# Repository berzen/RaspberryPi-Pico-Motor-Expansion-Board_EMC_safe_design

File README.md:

power supply: 
- 35mmx20mm instead of 55mmx22mm (43% reduction)
 - update of components:
    - ch224a vs ch224k (ch224k should be replaced regarding IC supplier)
    - 12pin USB vs 6pin USB (connection of USB lines - additional PD profiles possible)
    - impedance controlled connection for DP, DN, CC1, CC2 lines (for JLCPCB 2 layer stackup)
    - 20V VBUS vs 12V VBUS (less current)
    - LMR51635 vs TPS5450 (smaller size, less additional components)
    - cost reduction of BOM costs
    - 2 layer PCB vs 4 layer PCB
    - EMC safe design

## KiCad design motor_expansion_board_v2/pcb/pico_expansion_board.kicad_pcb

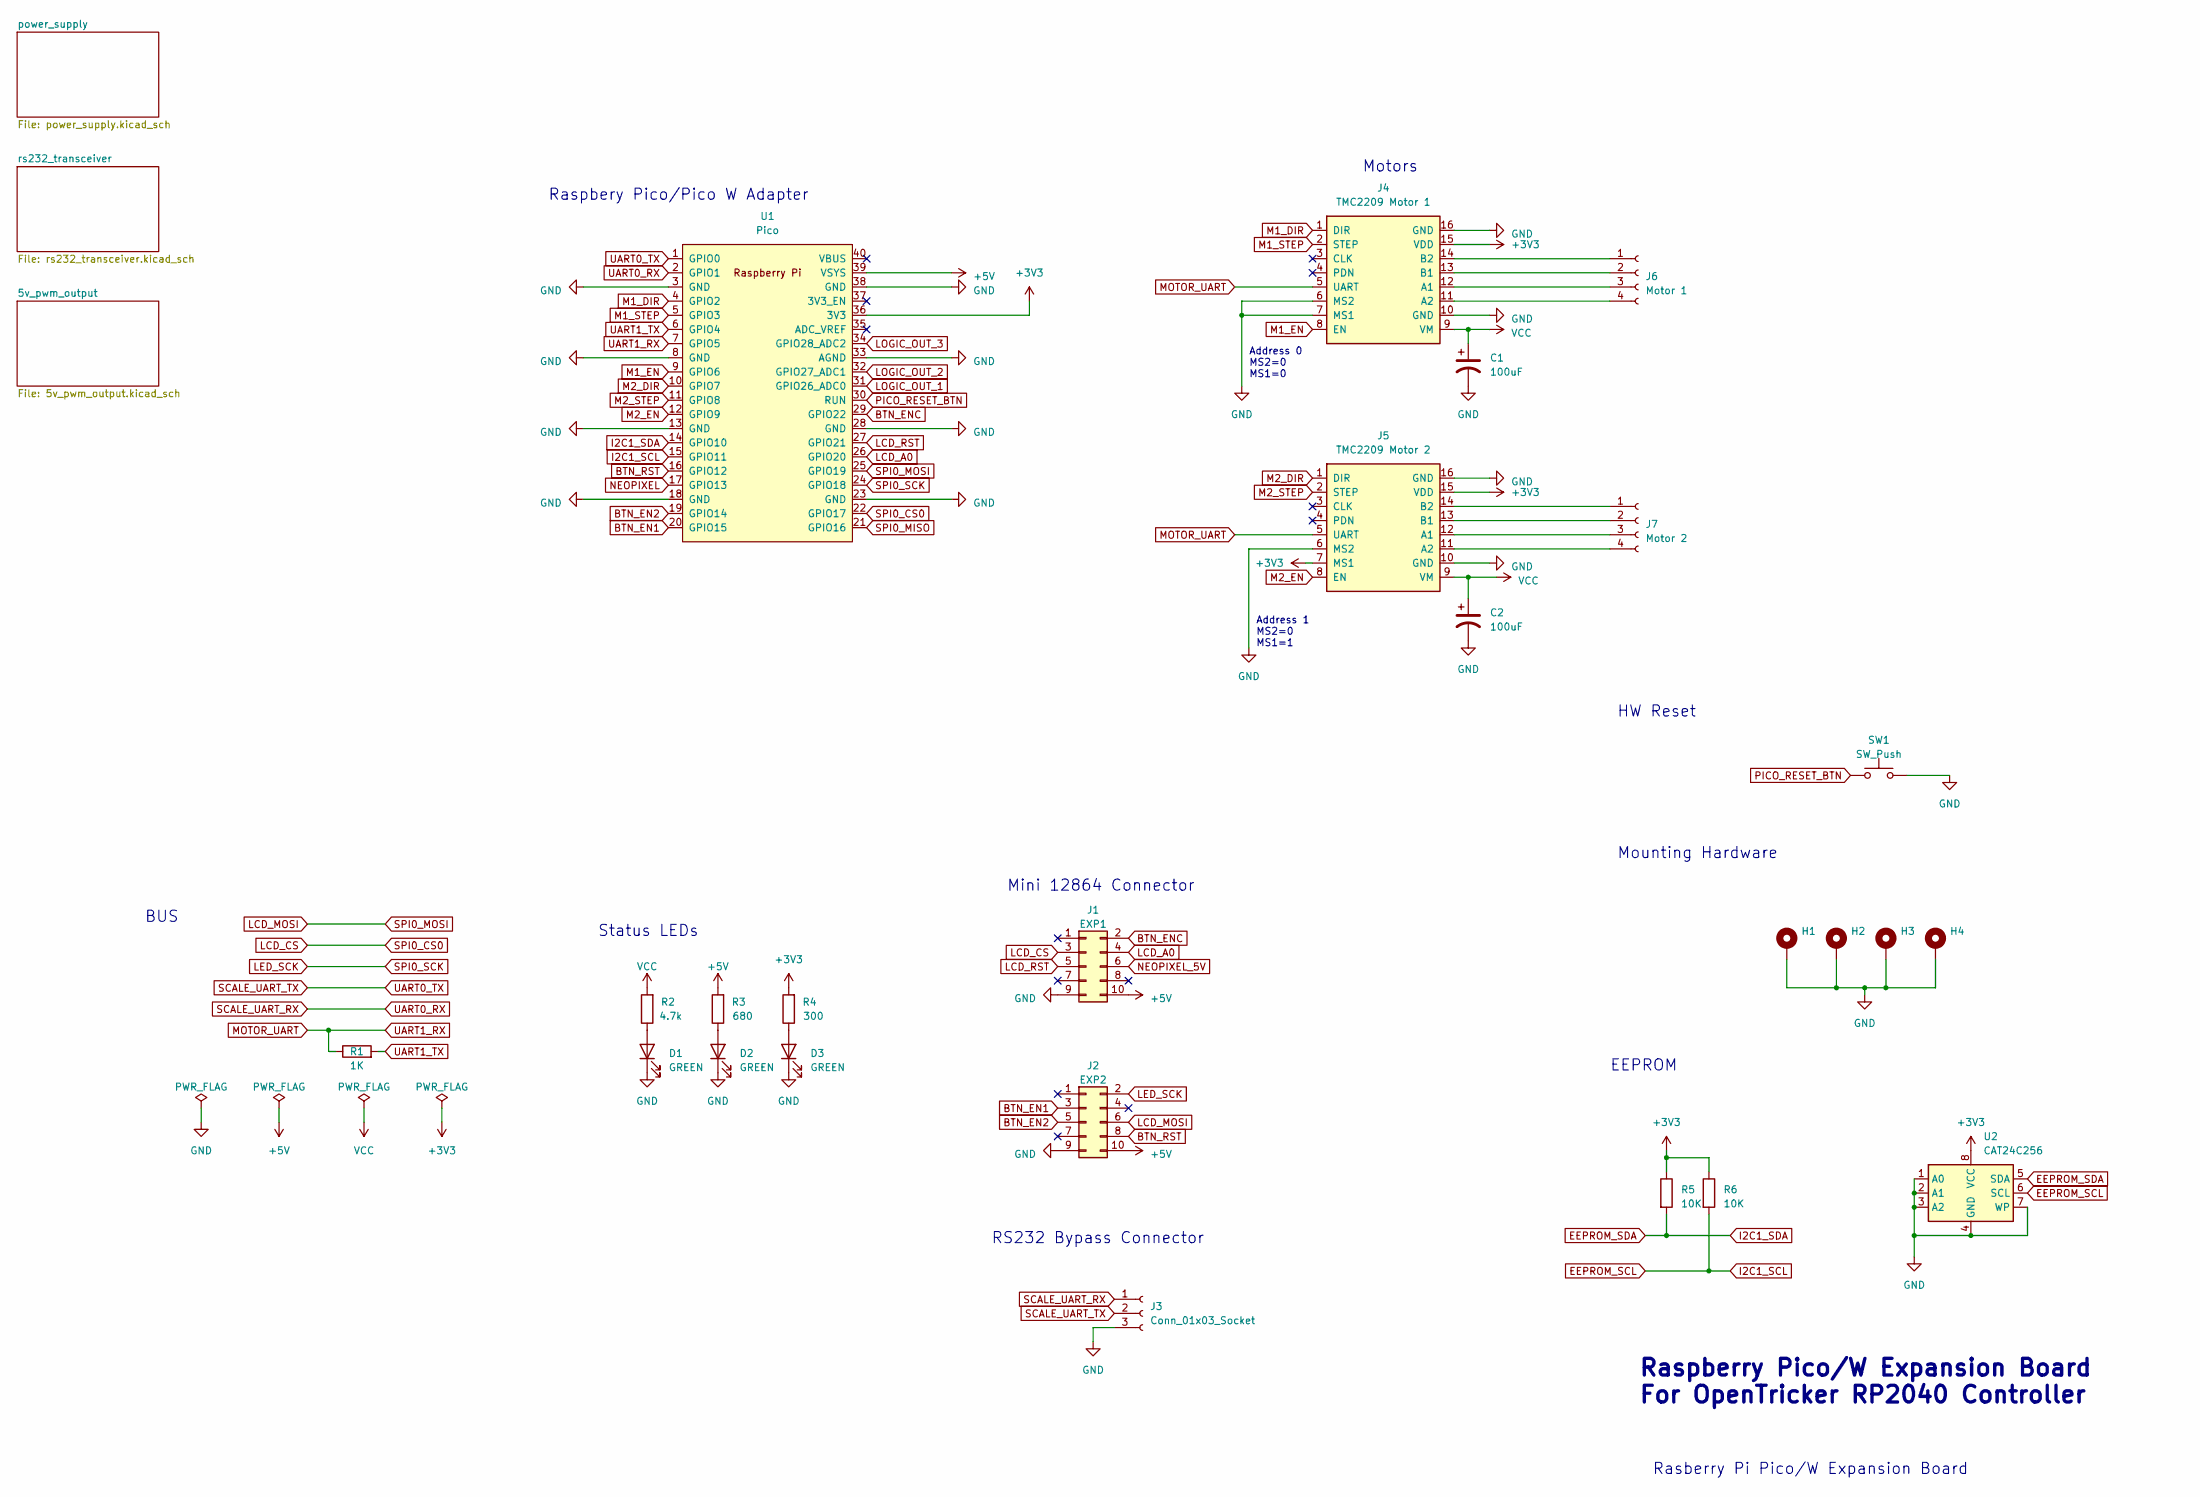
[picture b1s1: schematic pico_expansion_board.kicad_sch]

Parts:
C1, C2: 100uF; CP_Elec_6.3x7.7; LCSC Part # C2836442
D1, D2, D3: GREEN; D_0805_2012Metric_Pad1.15x1.40mm_HandSolder; LCSC Part # C84257
H1, H2, H3, H4: MountingHole_3.2mm_M3_Pad_Via
J1: EXP1; IDC-Header_2x05_P2.54mm_Vertical; LCSC Part # C2977596
J2: EXP2; IDC-Header_2x05_P2.54mm_Vertical; LCSC Part # C2977596
J3: Conn_01x03_Socket; JST_XH_B3B-XH-A_1x03_P2.50mm_Vertical; LCSC Part # C158003
J4: TMC2209 Motor 1; Conn_StepStick_smaller_hole; LCSC Part # C27438
J5: TMC2209 Motor 2; Conn_StepStick_smaller_hole; LCSC Part # C27438
J6: Motor 1; JST_XH_B4B-XH-A_1x04_P2.50mm_Vertical; LCSC Part # C144395
J7: Motor 2; JST_XH_B4B-XH-A_1x04_P2.50mm_Vertical; LCSC Part # C144395
R1: 1K; R_0805_2012Metric_Pad1.20x1.40mm_HandSolder; LCSC Part # C17513
R2: 4.7k; R_0805_2012Metric_Pad1.20x1.40mm_HandSolder; LCSC Part # C17673
R3: 680; R_0805_2012Metric_Pad1.20x1.40mm_HandSolder; LCSC Part # C17798
R4: 300; R_0805_2012Metric_Pad1.20x1.40mm_HandSolder; LCSC Part # C17617
R5, R6: 10K; R_0805_2012Metric_Pad1.20x1.40mm_HandSolder; LCSC Part # C17414
SW1: SW_Push; SW_Push_1P1T_NO_6x6mm_H9.5mm; LCSC Part # C2837532
U1: Pico; RPi_Pico_FootprintOnly; LCSC Part # C429947
U2: CAT24C256; SO-8_3.9x4.9mm_P1.27mm; LCSC Part # C79987

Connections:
+3V3: J4.15 (VDD), J5.7 (MS1), J5.15 (VDD), R4.2, R5.1, R6.1, U1.36 (3V3), U2.8 (VCC); also elsewhere on the board
+5V: J1.10, J2.10, R3.2, U1.39 (VSYS); also elsewhere on the board
BTN_EN1: J2.3, U1.20 (GPIO15)
BTN_EN2: J2.5, U1.19 (GPIO14)
BTN_ENC: J1.2, U1.29 (GPIO22)
BTN_RST: J2.8, U1.16 (GPIO12)
EEPROM_SCL: R6.2, U1.15 (GPIO11), U2.6 (SCL)
EEPROM_SDA: R5.2, U1.14 (GPIO10), U2.5 (SDA)
GND: C1.2, C2.2, D1.1 (K), D2.1 (K), D3.1 (K), H1.1, H2.1, H3.1, H4.1, J1.9, J2.9, J3.3, J4.6 (MS2), J4.7 (MS1), J4.10 (GND), J4.16 (GND), J5.6 (MS2), J5.10 (GND), J5.16 (GND), SW1.2, U1.3 (GND), U1.8 (GND), U1.13 (GND), U1.18 (GND), U1.23 (GND), U1.28 (GND), U1.33 (AGND), U1.38 (GND), U2.1 (A0), U2.2 (A1), U2.3 (A2), U2.4 (GND), U2.7 (WP); also elsewhere on the board
LCD_A0: J1.4, U1.26 (GPIO20)
LCD_CS: J1.3, U1.22 (GPIO17)
LCD_MOSI: J2.6, U1.25 (GPIO19)
LCD_RST: J1.5, U1.27 (GPIO21)
LED_SCK: J2.2, U1.24 (GPIO18)
LOGIC_OUT_1: U1.31 (GPIO26_ADC0); also elsewhere on the board
LOGIC_OUT_2: U1.32 (GPIO27_ADC1); also elsewhere on the board
LOGIC_OUT_3: U1.34 (GPIO28_ADC2); also elsewhere on the board
M1_DIR: J4.1 (DIR), U1.4 (GPIO2)
M1_EN: J4.8 (EN), U1.9 (GPIO6)
M1_STEP: J4.2 (STEP), U1.5 (GPIO3)
M2_DIR: J5.1 (DIR), U1.10 (GPIO7)
M2_EN: J5.8 (EN), U1.12 (GPIO9)
M2_STEP: J5.2 (STEP), U1.11 (GPIO8)
MOTOR_UART: J4.5 (UART), J5.5 (UART), R1.1, U1.7 (GPIO5)
NEOPIXEL: U1.17 (GPIO13); also elsewhere on the board
NEOPIXEL_5V: J1.6; also elsewhere on the board
unnamed: D1.2 (A), R2.1
unnamed: D2.2 (A), R3.1
unnamed: D3.2 (A), R4.1
unnamed: J4.12 (A1), J6.3
unnamed: J4.11 (A2), J6.4
unnamed: J4.13 (B1), J6.2
unnamed: J4.14 (B2), J6.1
unnamed: J5.12 (A1), J7.3
unnamed: J5.11 (A2), J7.4
unnamed: J5.13 (B1), J7.2
unnamed: J5.14 (B2), J7.1
PICO_RESET_BTN: SW1.1, U1.30 (RUN)
SCALE_UART_RX: J3.1, U1.2 (GPIO1); also elsewhere on the board
SCALE_UART_TX: J3.2, U1.1 (GPIO0); also elsewhere on the board
SPI0_MISO: U1.21 (GPIO16)
UART1_TX: R1.2, U1.6 (GPIO4)
VBUS: C1.1, C2.1, J4.9 (VM), J5.9 (VM), R2.2; also elsewhere on the board

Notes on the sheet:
Motors
Address 1 MS2=0 MS1=1
BUS
Mounting Hardware
EEPROM
Mini 12864 Connector
Raspberry Pico/W Expansion Board For OpenTricker RP2040 Controller
RS232 Bypass Connector
Rasberry Pi Pico/W Expansion Board
HW Reset
Raspbery Pico/Pico W Adapter
Status LEDs
Address 0 MS2=0 MS1=0

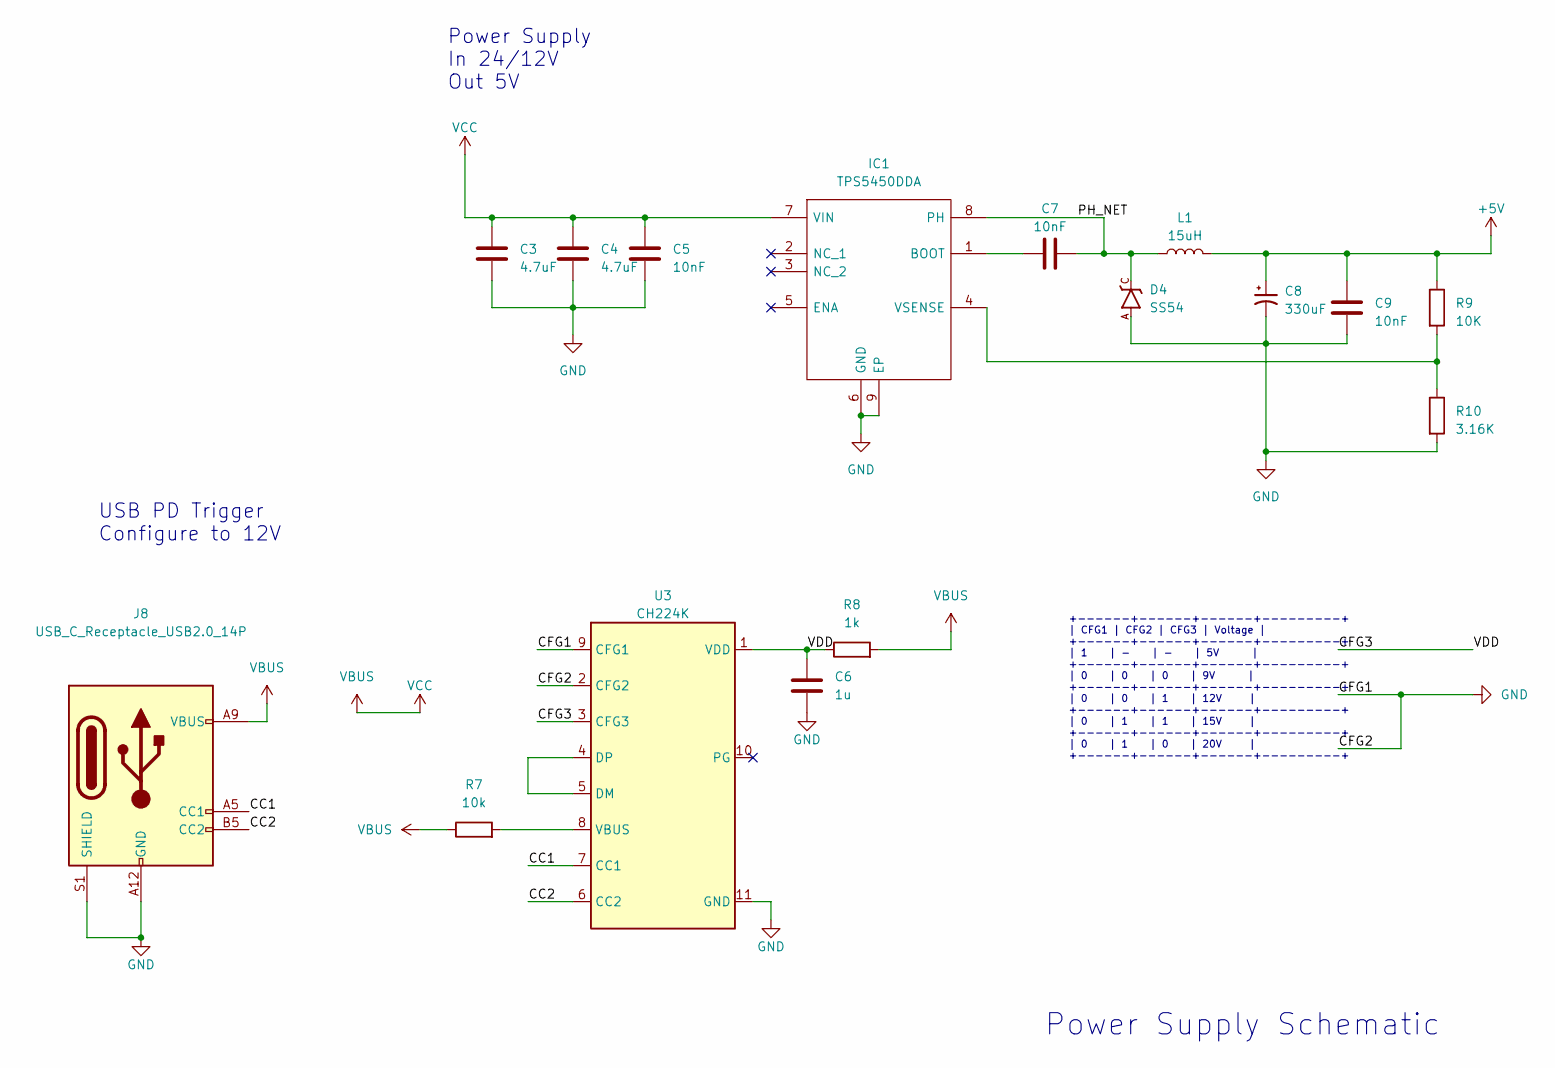
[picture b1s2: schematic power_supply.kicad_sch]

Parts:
C3, C4: 4.7uF; C_0805_2012Metric_Pad1.18x1.45mm_HandSolder; LCSC Part # C98192
C5, C7, C9: 10nF; C_0805_2012Metric_Pad1.18x1.45mm_HandSolder; LCSC Part # C1710
C6: 1u; C_0805_2012Metric_Pad1.18x1.45mm_HandSolder; LCSC Part # C28323
C8: 330uF; CP_Elec_10x10.5; LCSC Part # C19606
D4: SS54; DO-214AC; LCSC Part # C22452
IC1: TPS5450DDA; SOIC127P600X170-9N; Mouser Part Number 595-TPS5450DDA
J8: USB_C_Receptacle_USB2.0_14P; USB_C_Receptacle_HRO_TYPE-C-31-M-17; LCSC Part # C668623
L1: 15uH; Power Inductor 10x11; LCSC Part # C151872
R7: 10k; R_0805_2012Metric_Pad1.20x1.40mm_HandSolder; LCSC Part # C17414
R8: 1k; R_0805_2012Metric_Pad1.20x1.40mm_HandSolder; LCSC Part # C17513
R9: 10K; R_0805_2012Metric_Pad1.20x1.40mm_HandSolder; LCSC Part # C17414
R10: 3.16K; R_0805_2012Metric_Pad1.20x1.40mm_HandSolder; LCSC Part # C52603
U3: CH224K; SSOP-10-1EP_3.9x4.9mm_P1mm_EP2.1x3.3mm; LCSC Part # C970725

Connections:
+5V: C8.1, C9.1, L1.2, R9.1; also elsewhere on the board
/power_supply/CC1: J8.A5 (CC1), U3.7 (CC1)
/power_supply/CC2: J8.B5 (CC2), U3.6 (CC2)
/power_supply/CFG3: C6.1, R8.1, U3.1 (VDD), U3.3 (CFG3)
/power_supply/PH_NET: C7.2, D4.C, IC1.8 (PH), L1.1
GND: C3.2, C4.2, C5.2, C6.2, C8.2, C9.2, D4.A, IC1.6 (GND), IC1.9 (EP), J8.A12 (GND), J8.B12 (GND), J8.S1 (SHIELD), R10.2, U3.2 (CFG2), U3.9 (CFG1), U3.11 (GND); also elsewhere on the board
unnamed: C7.1, IC1.1 (BOOT)
unnamed: IC1.4 (VSENSE), R9.2, R10.1
unnamed: U3.4 (DP), U3.5 (DM)
unnamed: R7.2, U3.8 (VBUS)
VBUS: C3.1, C4.1, C5.1, IC1.7 (VIN), J8.A9 (VBUS), J8.B9 (VBUS), R7.1, R8.2; also elsewhere on the board

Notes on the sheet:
+------+------+------+---------+ | CFG1 | CFG2 | CFG3 | Voltage | +------+------+------+---------+ | 1 | - | - | 5V | +------+------+------+---------+ | 0 | 0 | 0 | 9V | +------+------+------+---------+ | 0 | 0 | 1 | 12V | +------+------+------+---------+ | 0 | 1 | 1 | 15V | +------+------+------+-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
Power Supply Schematic
USB PD Trigger Configure to 12V
Power Supply In 24/12V Out 5V

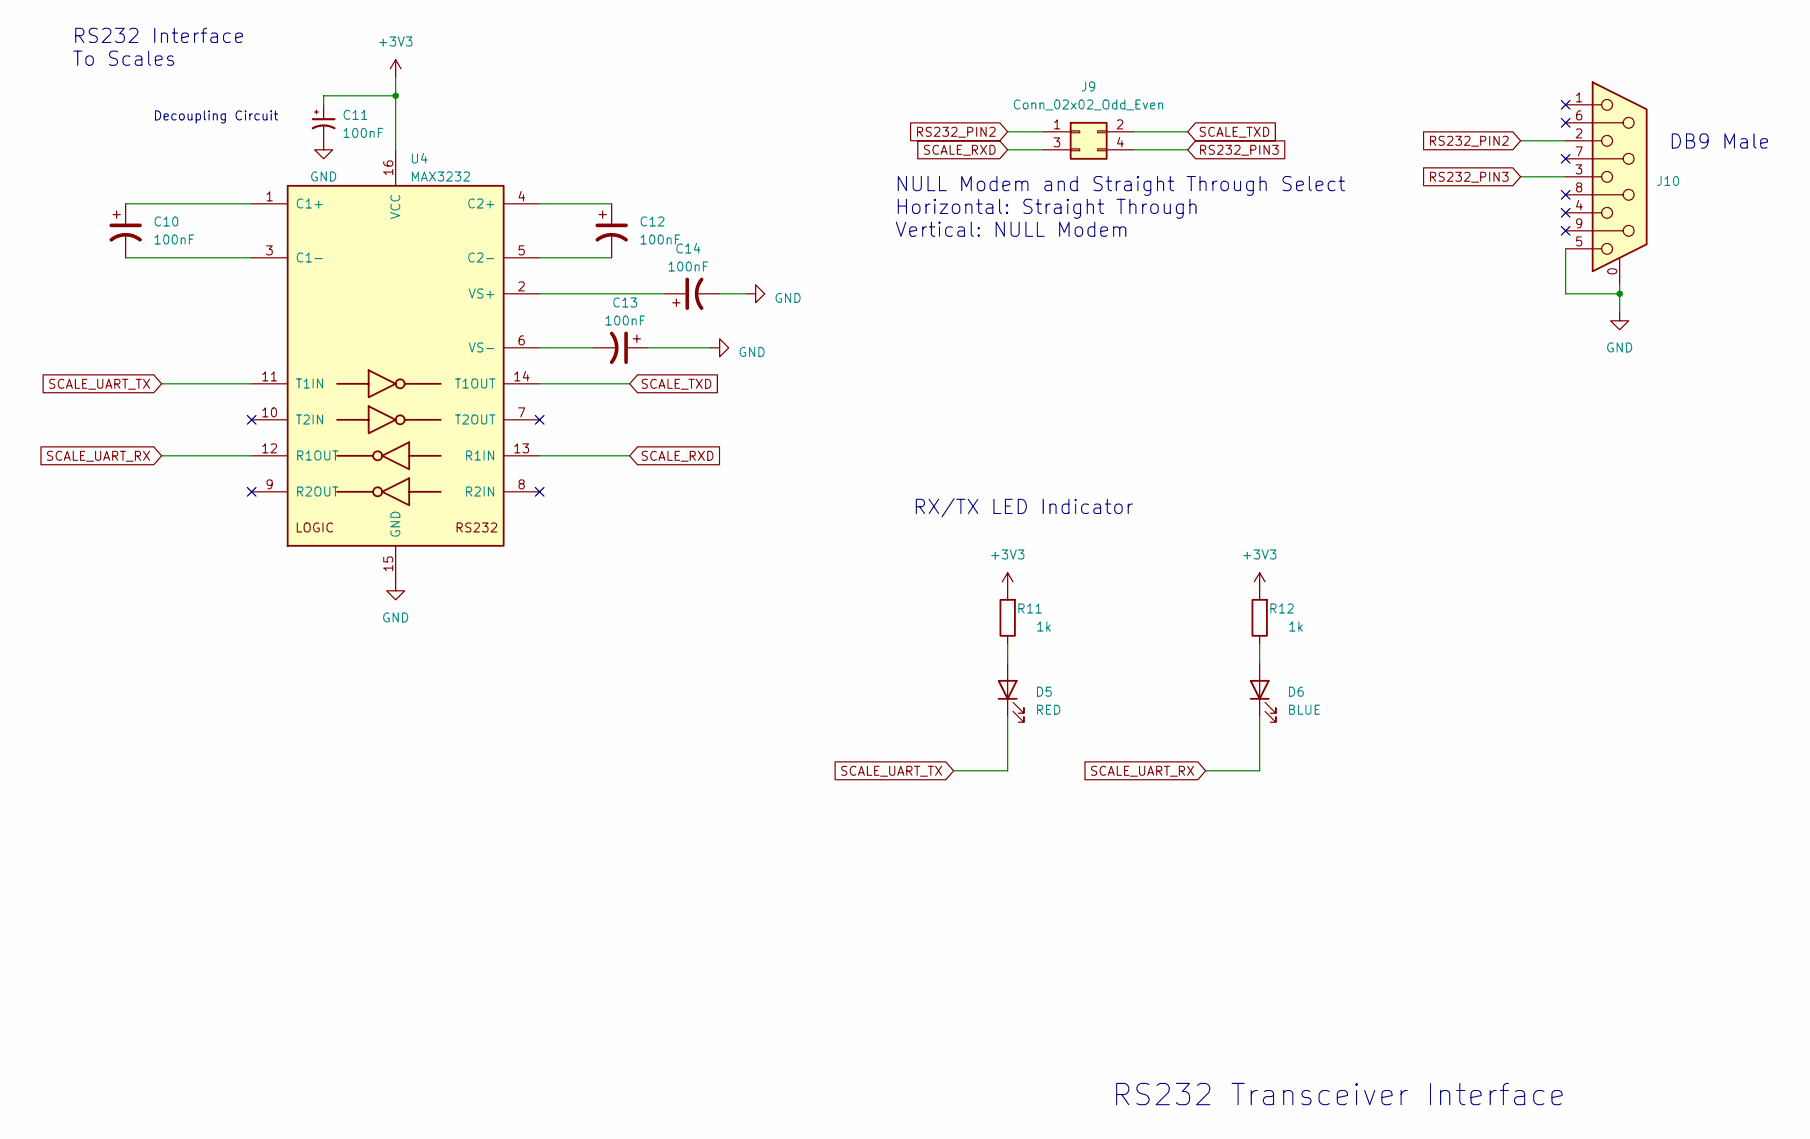
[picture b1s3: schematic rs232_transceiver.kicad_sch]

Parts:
C10, C11, C12, C13, C14: 100nF; C_0805_2012Metric_Pad1.18x1.45mm_HandSolder; LCSC Part # C49678
D5: RED; D_0805_2012Metric_Pad1.15x1.40mm_HandSolder; LCSC Part # C84256
D6: BLUE; D_0805_2012Metric_Pad1.15x1.40mm_HandSolder; LCSC Part # C965817
J9: Conn_02x02_Odd_Even; PinHeader_2x02_P2.00mm_Vertical; LCSC Part # C2935957
J10: DSUB-9_Male_Horizontal_P2.77x2.84mm_EdgePinOffset7.70mm_Hou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; LCSC Part # C426221
R11, R12: 1k; R_0805_2012Metric_Pad1.20x1.40mm_HandSolder; LCSC Part # C17513
U4: MAX3232; SOIC-16_3.9x9.9mm_P1.27mm; LCSC Part # C18261

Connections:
+3V3: C11.1, R11.2, R12.2, U4.16 (VCC); also elsewhere on the board
GND: C11.2, C13.1, C14.2, J10.0 (PAD), J10.5, U4.15 (GND); also elsewhere on the board
unnamed: D5.2 (A), R11.1
unnamed: D6.2 (A), R12.1
unnamed: C10.1, U4.1 (C1+)
unnamed: C10.2, U4.3 (C1-)
unnamed: C12.1, U4.4 (C2+)
unnamed: C12.2, U4.5 (C2-)
unnamed: C14.1, U4.2 (VS+)
unnamed: C13.2, U4.6 (VS-)
RS232_PIN2: J9.1, J10.2
RS232_PIN3: J9.4, J10.3
SCALE_RXD: J9.3, U4.13 (R1IN)
SCALE_TXD: J9.2, U4.14 (T1OUT)
SCALE_UART_RX: D6.1 (K), U4.12 (R1OUT); also elsewhere on the board
SCALE_UART_TX: D5.1 (K), U4.11 (T1IN); also elsewhere on the board

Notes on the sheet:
RS232 Interface To Scales
RX/TX LED Indicator
DB9 Male
Decoupling Circuit
NULL Modem and Straight Through Select Horizontal: Straight Through Vertical: NULL Modem
RS232 Transceiver Interface

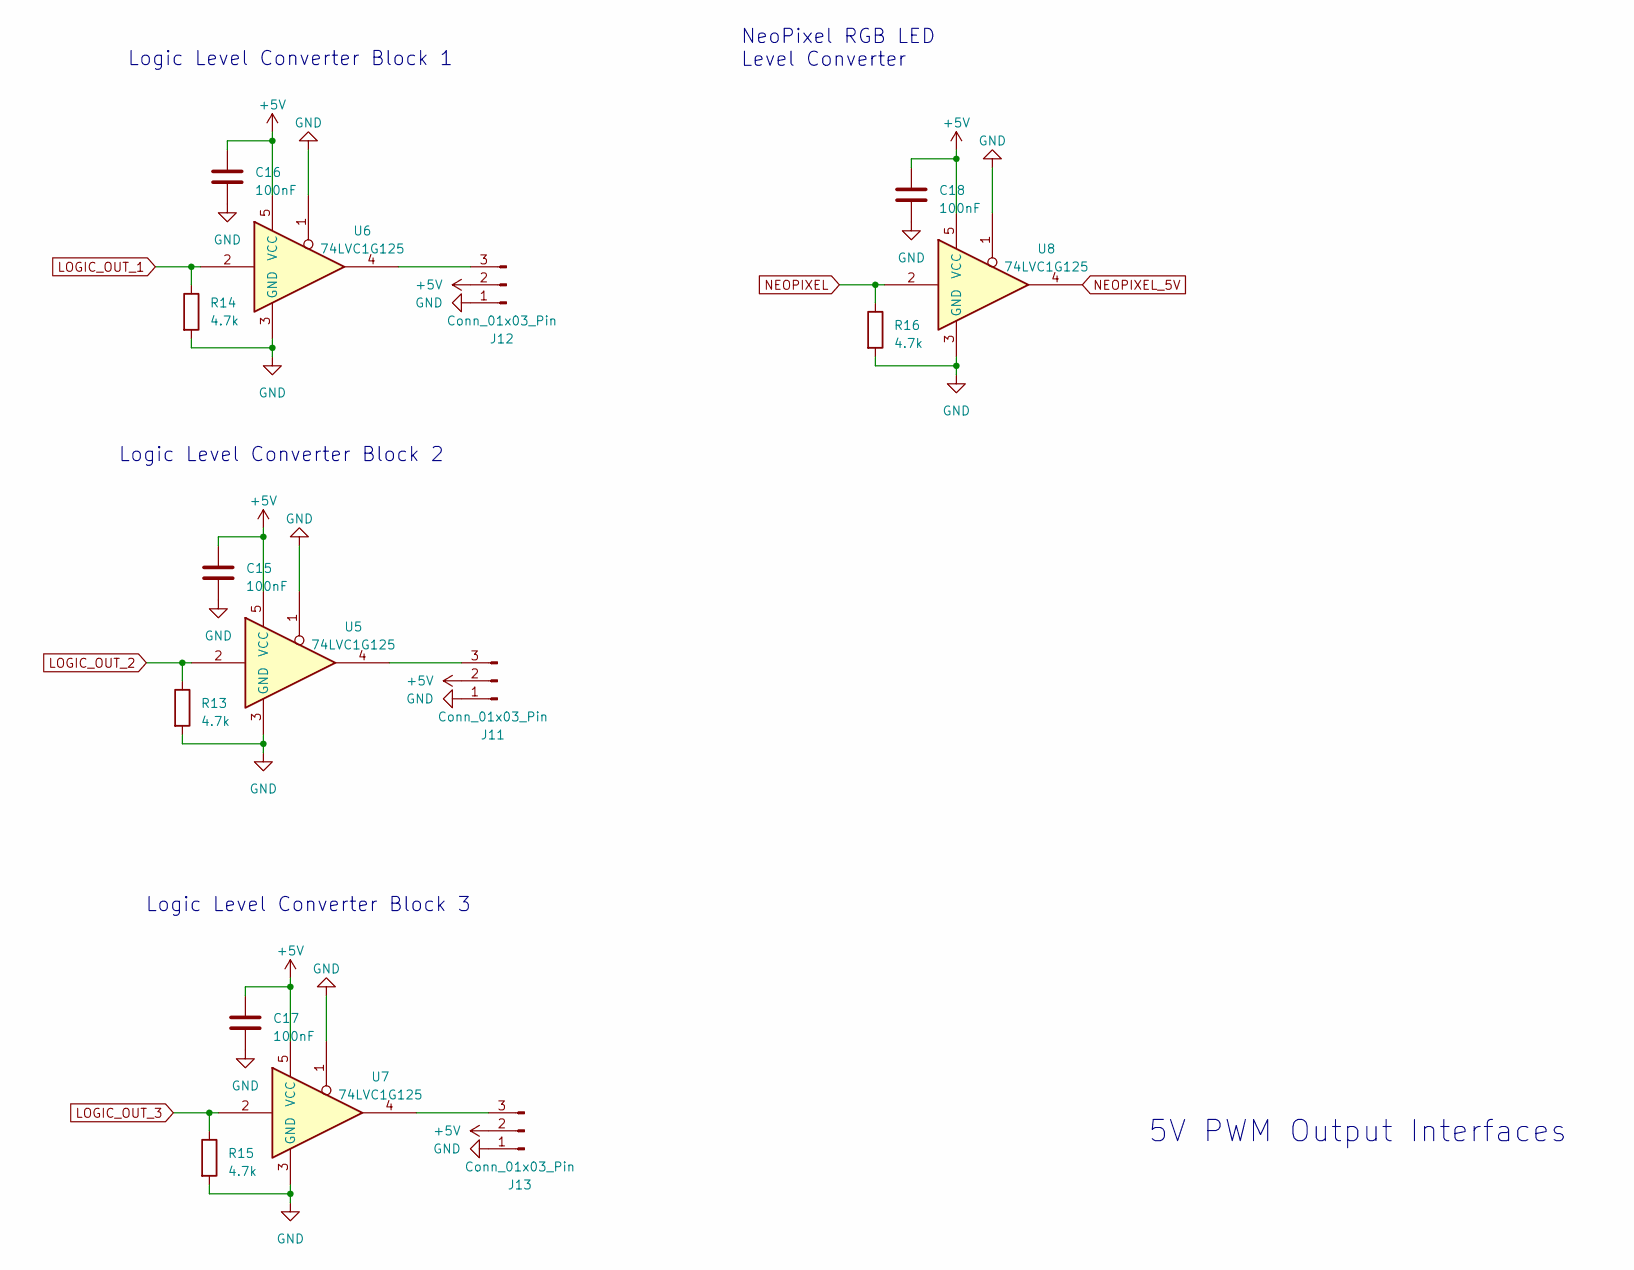
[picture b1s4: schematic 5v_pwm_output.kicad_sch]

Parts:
C15, C16, C17, C18: 100nF; C_0805_2012Metric_Pad1.18x1.45mm_HandSolder; LCSC Part # C49678
J11, J12, J13: Conn_01x03_Pin; JST_XH_B3B-XH-A_1x03_P2.50mm_Vertical; LCSC Part # C158003
R13, R14, R15, R16: 4.7k; R_0805_2012Metric_Pad1.20x1.40mm_HandSolder; LCSC Part # C17673
U5, U6, U7, U8: 74LVC1G125; SOT-23-5; LCSC Part # C23654

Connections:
+5V: C15.1, C16.1, C17.1, C18.1, J11.2, J12.2, J13.2, U5.5 (VCC), U6.5 (VCC), U7.5 (VCC), U8.5 (VCC); also elsewhere on the board
GND: C15.2, C16.2, C17.2, C18.2, J11.1, J12.1, J13.1, R13.2, R14.2, R15.2, R16.2, U5.1, U5.3 (GND), U6.1, U6.3 (GND), U7.1, U7.3 (GND), U8.1, U8.3 (GND); also elsewhere on the board
LOGIC_OUT_1: R14.1, U6.2; also elsewhere on the board
LOGIC_OUT_2: R13.1, U5.2; also elsewhere on the board
LOGIC_OUT_3: R15.1, U7.2; also elsewhere on the board
NEOPIXEL: R16.1, U8.2; also elsewhere on the board
NEOPIXEL_5V: U8.4; also elsewhere on the board
unnamed: J11.3, U5.4
unnamed: J12.3, U6.4
unnamed: J13.3, U7.4

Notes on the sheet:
Logic Level Converter Block 2
NeoPixel RGB LED Level Converter
5V PWM Output Interfaces
Logic Level Converter Block 1
Logic Level Converter Block 3

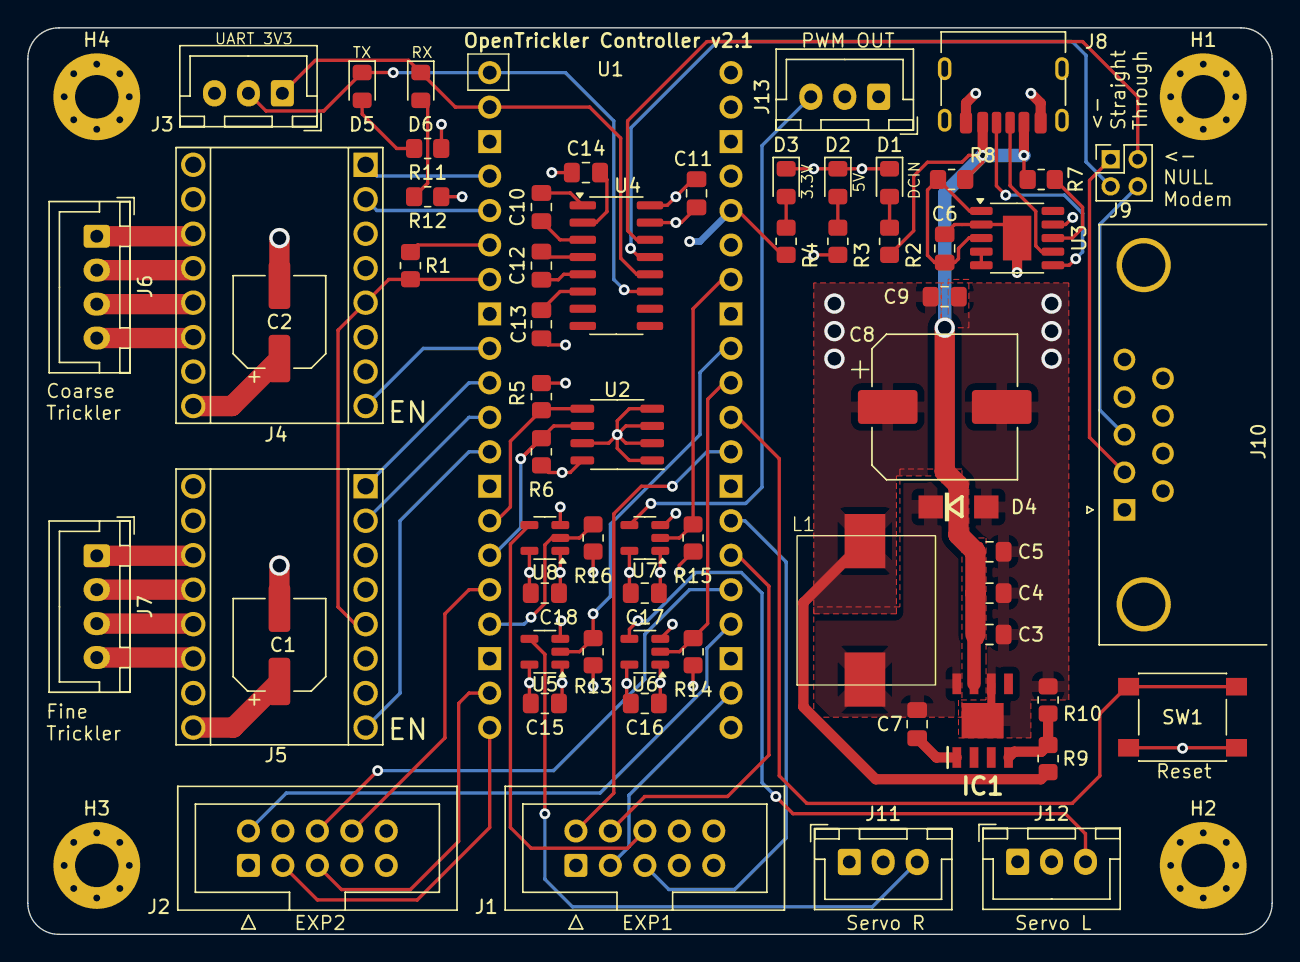
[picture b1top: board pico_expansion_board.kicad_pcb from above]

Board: 4 copper layers, 91.7 x 66.8 mm, 68 parts (0 on the bottom side), 65 nets.

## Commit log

2025-07-20 kicad version updated
2025-07-20 initial
